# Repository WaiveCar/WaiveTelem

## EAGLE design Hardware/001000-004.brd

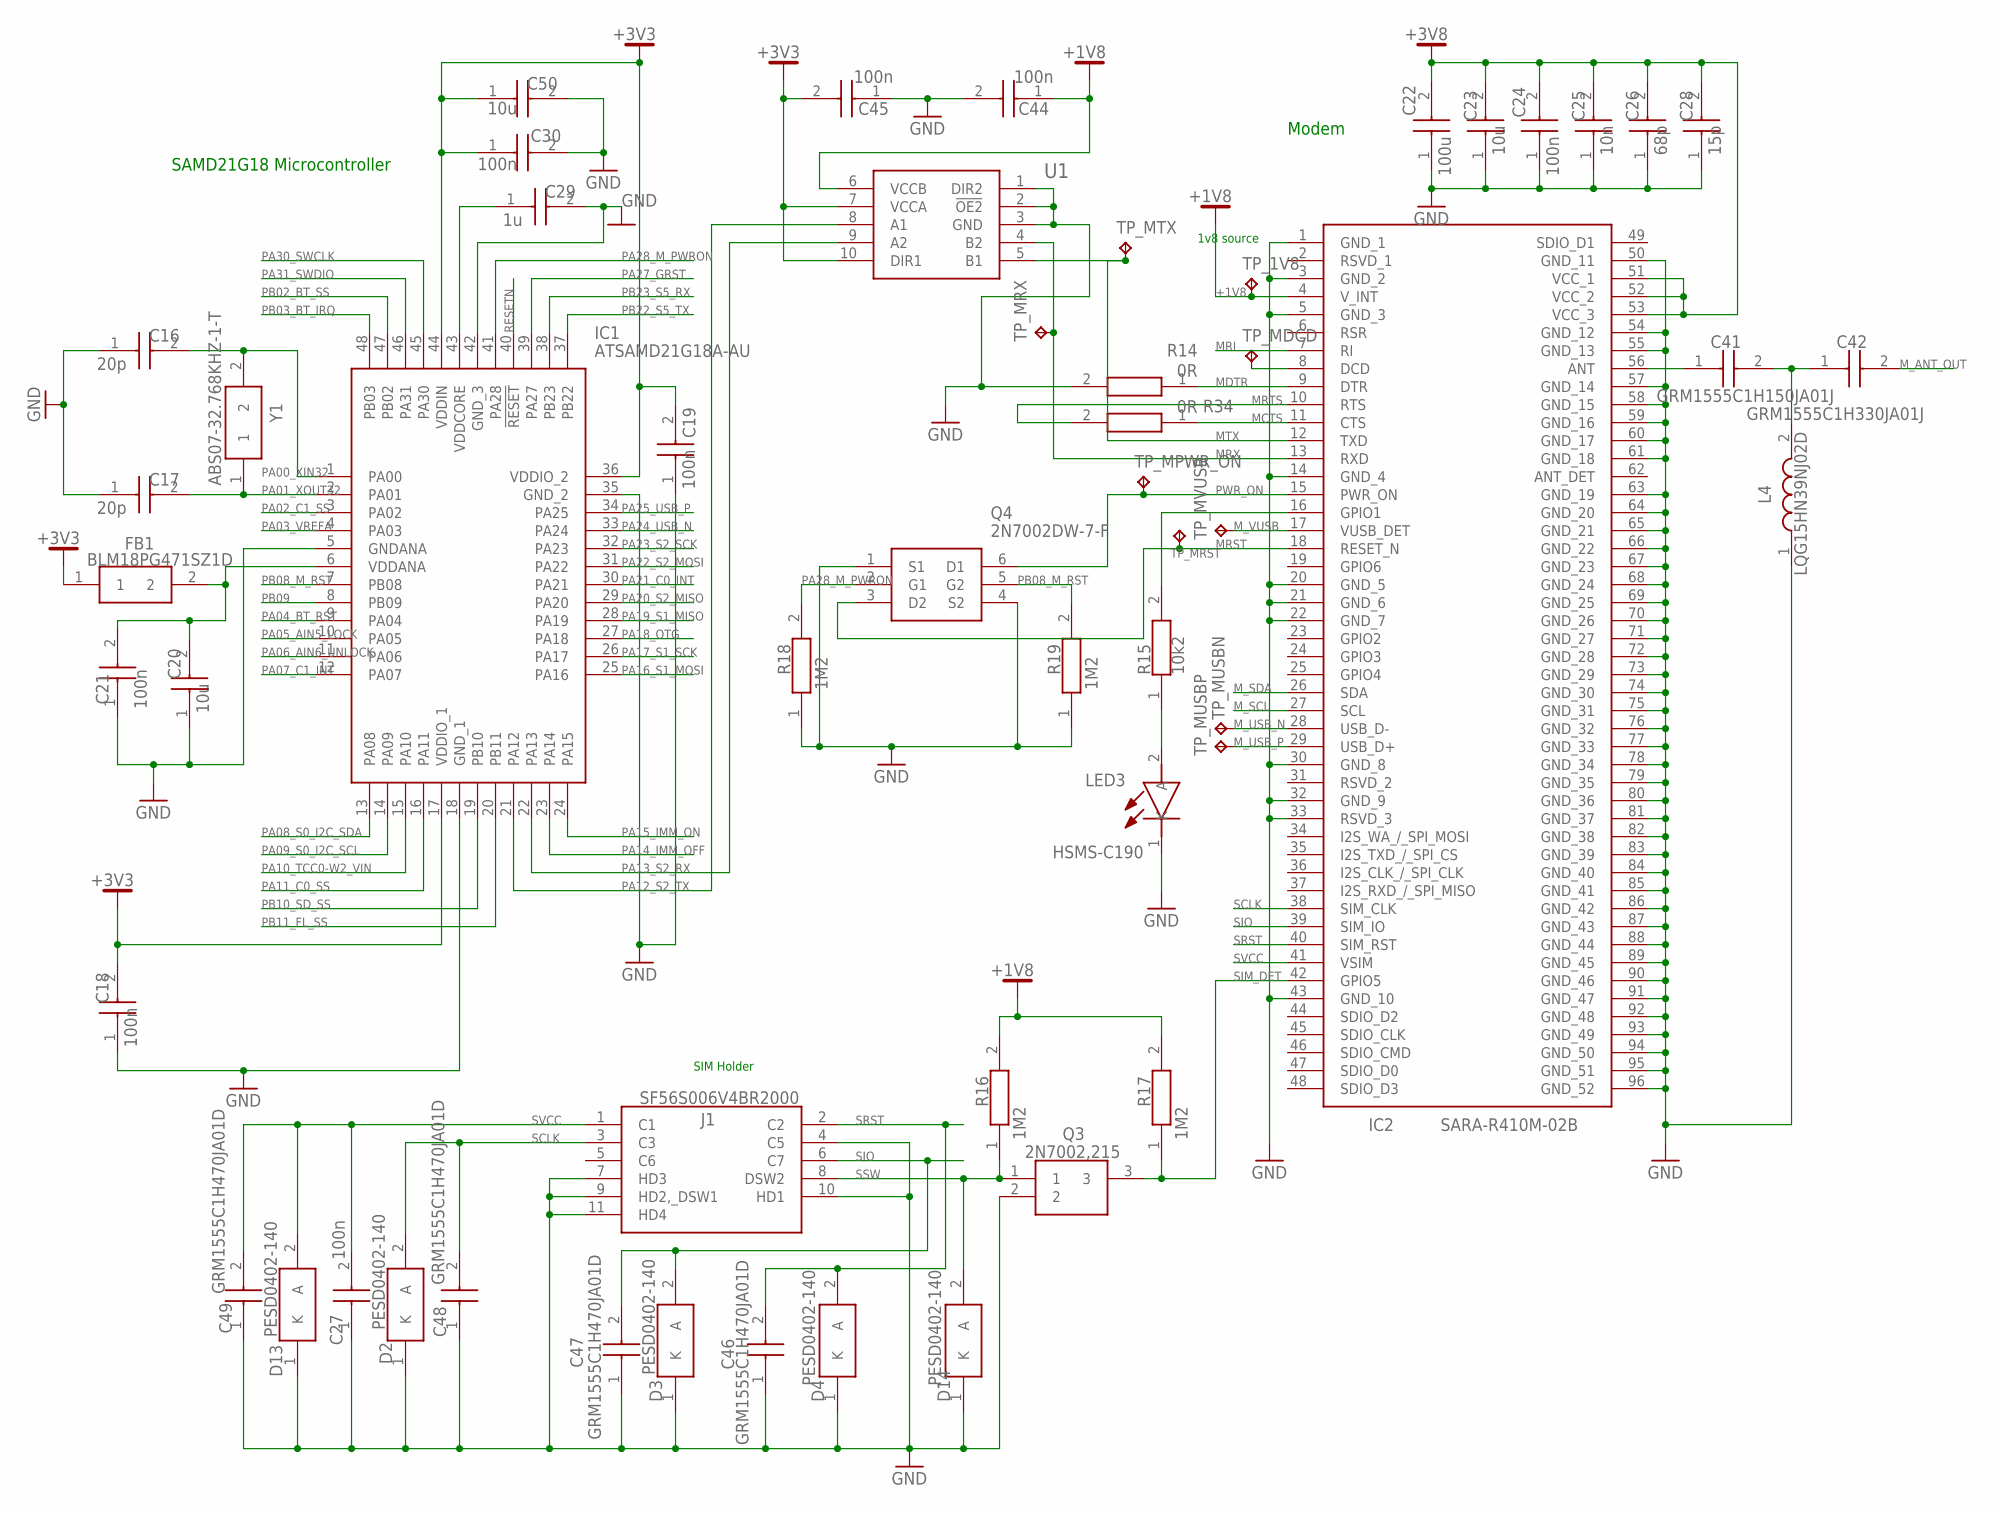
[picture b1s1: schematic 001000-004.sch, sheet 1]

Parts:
C16, C17: 20p; CAPC1005X55N
C18, C19, C21, C24, C27, C30, C44, C45: 100n; CAPC1005X55N
C20, C23, C50: 10u; CAPC1608X90N
C22: 100u; CAPC3216X180N
C25: 10n; CAPC1005X55N
C26: 68p; CAPC1005X55N
C28: 15p; CAPC1005X55N
C29: 1u; CAPC1005X55N
C41: GRM1555C1H150JA01J; CAPC1005X55N
C42: GRM1555C1H330JA01J; CAPC1005X55N
C46, C47, C48, C49: GRM1555C1H470JA01D; CAPC1005X55N
D2, D3, D4, D13, D14: PESD0402-140; DIONC1005X43N
FB1: BLM18PG471SZ1D; BEADC1608X95N
IC1: ATSAMD21G18A-AU; QFP50P900X900X120-48N
IC2: SARA-R410M-02B; SARA-U201-03B
J1: SF56S006V4BR2000
L4: LQG15HN39NJ02D; INDC1005X55N
LED3: HSMS-C190; LEDC1608X90N
Q3: 2N7002,215; SOT95P230X110-3N
Q4: 2N7002DW-7-F; SOT65P210X100-6N
R14, R34: 0R; RESC1005X40N
R15: 10k2; RESC1005X40N
R16, R17, R18, R19: 1M2; RESC1005X40N
TP_1V8: TPB1,27; B1,27
TP_MDCD: TPB1,27; B1,27
TP_MPWR_ON: TPB1,27; B1,27
TP_MRST: TPB1,27; B1,27
TP_MRX: TPB1,27; B1,27
TP_MTX: TPB1,27; B1,27
TP_MUSBN: TPB1,27; B1,27
TP_MUSBP: TPB1,27; B1,27
TP_MVUSB: TPB1,27; B1,27
U1: SN74AVC2T245RSWR; RSW(RPUQFNN10)
Y1: ABS07-32.768KHZ-1-T; ABS0716632768KHZT

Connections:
+1V8: C44.1, IC2.4 (V_INT), R16.2, R17.2, TP_1V8.TP, U1.6 (VCCB)
+3V3: C18.2, C19.2, C30.1, C45.2, C50.1, FB1.1, IC1.17 (VDDIO_1), IC1.36 (VDDIO_2), IC1.44 (VDDIN), U1.7 (VCCA), U1.10 (DIR1); also elsewhere on the board
+3V8: C22.2, C23.2, C24.2, C25.2, C26.2, C28.2, IC2.51 (VCC_1), IC2.52 (VCC_2), IC2.53 (VCC_3); also elsewhere on the board
GND: C16.1, C17.1, C18.1, C19.1, C20.1, C21.1, C22.1, C23.1, C24.1, C25.1, C26.1, C27.1, C28.1, C29.2, C30.2, C44.2, C45.1, C46.1, C47.1, C48.1, C49.1, C50.2, D2.1 (K), D3.1 (K), D4.1 (K), D13.1 (K), D14.1 (K), IC1.5 (GNDANA), IC1.18 (GND_1), IC1.35 (GND_2), IC1.42 (GND_3), IC2.1 (GND_1), IC2.3 (GND_2), IC2.5 (GND_3), IC2.14 (GND_4), IC2.20 (GND_5), IC2.21 (GND_6), IC2.22 (GND_7), IC2.30 (GND_8), IC2.32 (GND_9), IC2.33 (RSVD_3), IC2.43 (GND_10), IC2.50 (GND_11), IC2.54 (GND_12), IC2.55 (GND_13), IC2.57 (GND_14), IC2.58 (GND_15), IC2.59 (GND_16), IC2.60 (GND_17), IC2.61 (GND_18), IC2.63 (GND_19), IC2.64 (GND_20), IC2.65 (GND_21), IC2.66 (GND_22), IC2.67 (GND_23), IC2.68 (GND_24), IC2.69 (GND_25), IC2.70 (GND_26), IC2.71 (GND_27), IC2.72 (GND_28), IC2.73 (GND_29), IC2.74 (GND_30), IC2.75 (GND_31), IC2.76 (GND_32), IC2.77 (GND_33), IC2.78 (GND_34), IC2.79 (GND_35), IC2.80 (GND_36), IC2.81 (GND_37), IC2.82 (GND_38), IC2.83 (GND_39), IC2.84 (GND_40), IC2.85 (GND_41), IC2.86 (GND_42), IC2.87 (GND_43), IC2.88 (GND_44), IC2.89 (GND_45), IC2.90 (GND_46), IC2.91 (GND_47), IC2.92 (GND_48), IC2.93 (GND_49), IC2.94 (GND_50), IC2.95 (GND_51), IC2.96 (GND_52), J1.4 (C5), J1.7 (HD3), J1.9 (HD2,_DSW1), J1.10 (HD1), J1.11 (HD4), L4.1, LED3.1 (K), Q3.2, Q4.1 (S1), Q4.4 (S2), R14.2, R18.1, R19.1, U1.1 (DIR2), U1.2 (!OE2), U1.3 (GND); also elsewhere on the board
MCTS: IC2.11 (CTS), R34.1
MDTR: IC2.9 (DTR), R14.1
MRI: IC2.7 (RI)
MRST: IC2.18 (RESET_N), Q4.3 (D2), TP_MRST.TP
MRTS: IC2.10 (RTS), R34.2
MRX: IC2.13 (RXD), TP_MRX.TP, U1.4 (B2)
MTX: IC2.12 (TXD), TP_MTX.TP, U1.5 (B1)
M_ANT_OUT: C42.2; also elsewhere on the board
M_SCL: IC2.27 (SCL); also elsewhere on the board
M_SDA: IC2.26 (SDA); also elsewhere on the board
M_USB_N: IC2.28 (USB_D-), TP_MUSBN.TP
M_USB_P: IC2.29 (USB_D+), TP_MUSBP.TP
M_VUSB: IC2.17 (VUSB_DET), TP_MVUSB.TP
unnamed: C20.2, C21.2, FB1.2, IC1.6 (VDDANA)
unnamed: C41.1, IC2.56 (ANT)
unnamed: IC2.16 (GPIO1), R15.2
unnamed: LED3.2 (A), R15.1
unnamed: IC2.8 (DCD), TP_MDCD.TP
unnamed: C29.1, IC1.43 (VDDCORE)
unnamed: C41.2, C42.1, L4.2
PA00_XIN32: C16.2, IC1.1 (PA00), Y1.2
PA01_XOUT32: C17.2, IC1.2 (PA01), Y1.1
PA02_C1_SS: IC1.3 (PA02); also elsewhere on the board
PA03_VREFA: IC1.4 (PA03)
PA04_BT_RST: IC1.9 (PA04); also elsewhere on the board
PA05_AIN5_LOCK: IC1.10 (PA05); also elsewhere on the board
PA06_AIN6_UNLOCK: IC1.11 (PA06); also elsewhere on the board
PA07_C1_INT: IC1.12 (PA07); also elsewhere on the board
PA08_S0_I2C_SDA: IC1.13 (PA08); also elsewhere on the board
PA09_S0_I2C_SCL: IC1.14 (PA09); also elsewhere on the board
PA10_TCC0-W2_VIN: IC1.15 (PA10); also elsewhere on the board
PA11_C0_SS: IC1.16 (PA11); also elsewhere on the board
PA12_S2_TX: IC1.21 (PA12), U1.8 (A1)
PA13_S2_RX: IC1.22 (PA13), U1.9 (A2)
PA14_IMM_OFF: IC1.23 (PA14); also elsewhere on the board
PA15_IMM_ON: IC1.24 (PA15); also elsewhere on the board
PA16_S1_MOSI: IC1.25 (PA16); also elsewhere on the board
PA17_S1_SCK: IC1.26 (PA17); also elsewhere on the board
PA18_OTG: IC1.27 (PA18); also elsewhere on the board
PA19_S1_MISO: IC1.28 (PA19); also elsewhere on the board
PA20_S2_MISO: IC1.29 (PA20); also elsewhere on the board
PA21_C0_INT: IC1.30 (PA21); also elsewhere on the board
PA22_S2_MOSI: IC1.31 (PA22); also elsewhere on the board
PA23_S2_SCK: IC1.32 (PA23); also elsewhere on the board
PA24_USB_N: IC1.33 (PA24); also elsewhere on the board
PA25_USB_P: IC1.34 (PA25); also elsewhere on the board
PA27_GRST: IC1.39 (PA27); also elsewhere on the board
PA28_M_PWRON: IC1.41 (PA28), Q4.2 (G1), R18.2
PA30_SWCLK: IC1.45 (PA30); also elsewhere on the board
PA31_SWDIO: IC1.46 (PA31); also elsewhere on the board
PB02_BT_SS: IC1.47 (PB02); also elsewhere on the board
PB03_BT_IRQ: IC1.48 (PB03); also elsewhere on the board
PB08_M_RST: IC1.7 (PB08), Q4.5 (G2), R19.2
PB09: IC1.8 (PB09); also elsewhere on the board
PB10_SD_SS: IC1.19 (PB10); also elsewhere on the board
PB11_FL_SS: IC1.20 (PB11); also elsewhere on the board
PB22_S5_TX: IC1.37 (PB22); also elsewhere on the board
PB23_S5_RX: IC1.38 (PB23); also elsewhere on the board
PWR_ON: IC2.15 (PWR_ON), Q4.6 (D1), TP_MPWR_ON.TP
RESETN: IC1.40 (!RESET); also elsewhere on the board
SCLK: C48.2, D2.2 (A), IC2.38 (SIM_CLK), J1.3 (C3)
SIM_DET: IC2.42 (GPIO5), Q3.3, R17.1
SIO: C47.2, D3.2 (A), IC2.39 (SIM_IO), J1.6 (C7)
SRST: C46.2, D4.2 (A), IC2.40 (SIM_RST), J1.2 (C2)
SSW: D14.2 (A), J1.8 (DSW2), Q3.1, R16.1
SVCC: C27.2, C49.2, D13.2 (A), IC2.41 (VSIM), J1.1 (C1)

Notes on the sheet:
SAMD21G18 Microcontroller
Modem
1v8 source
SIM Holder

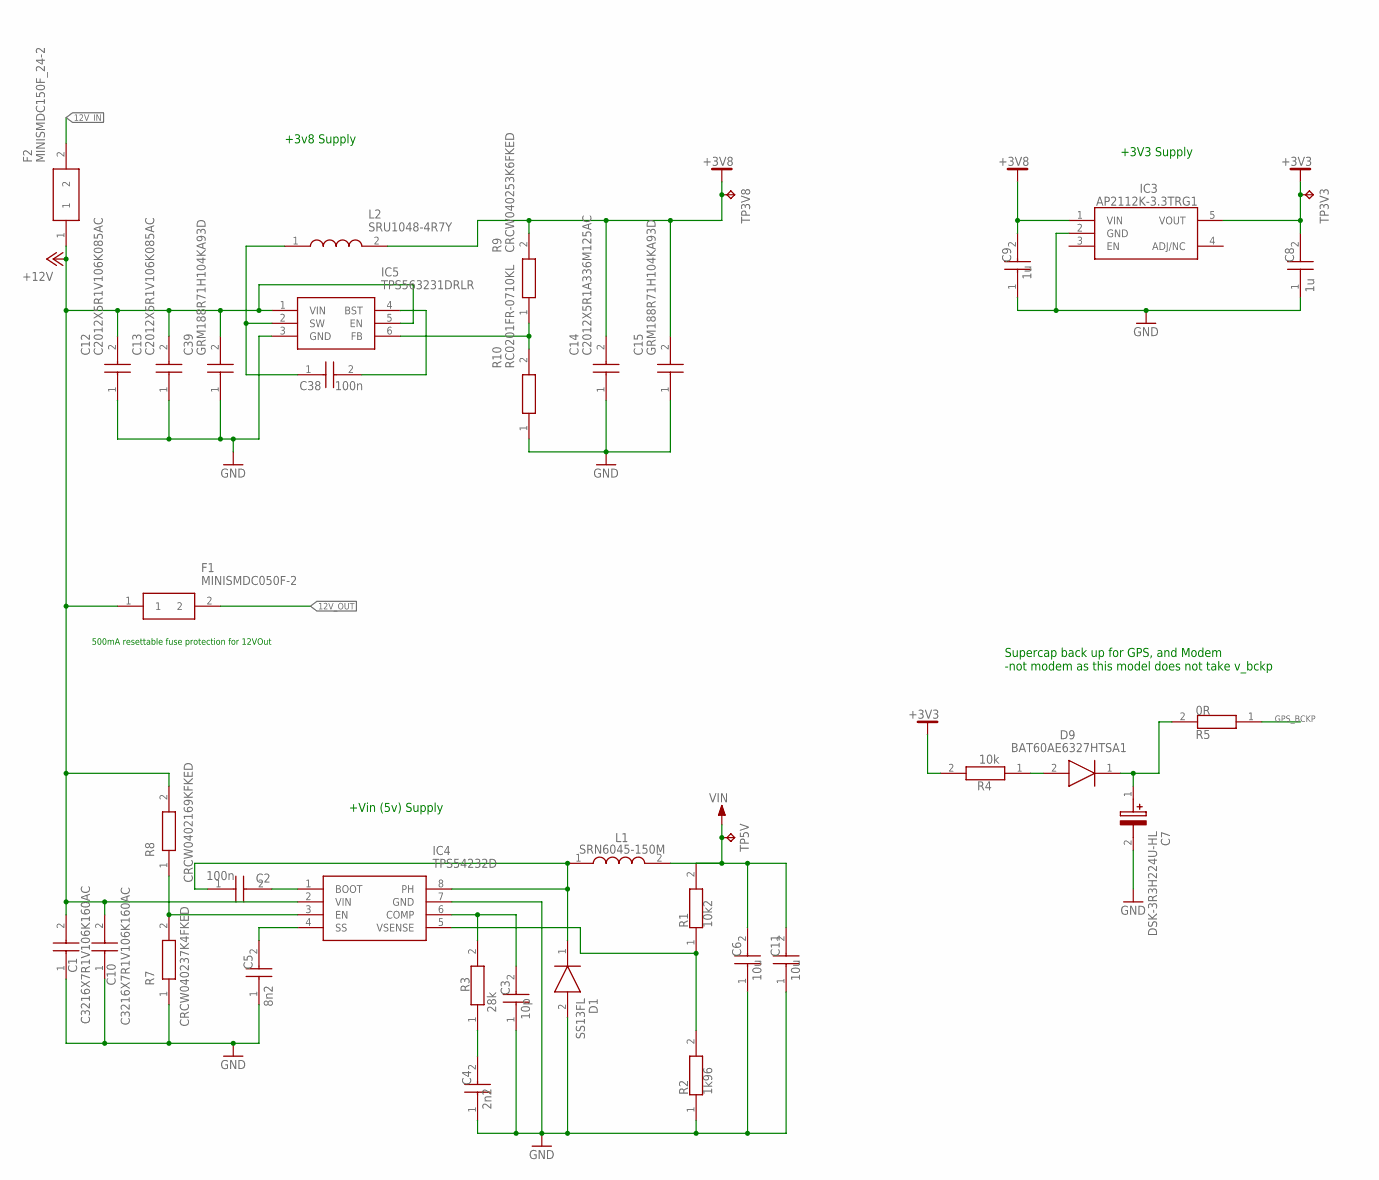
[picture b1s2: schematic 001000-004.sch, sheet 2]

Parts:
C1, C10: C3216X7R1V106K160AC; CAPC3216X180N
C2, C38: 100n; CAPC1005X55N
C3: 10p; CAPC1005X55N
C4: 2n2; CAPC1005X55N
C5: 8n2; CAPC1005X55N
C6, C11: 10u; CAPC2012X145N
C7: DSK-3R3H224U-HL; DSK-414_HL
C8, C9: 1u; CAPC1005X55N
C12, C13: C2012X5R1V106K085AC; CAPC2012X100N
C14: C2012X5R1A336M125AC; CAPC2012X145N
C15, C39: GRM188R71H104KA93D; CAPC1608X90N
D1: SS13FL; SODFL3617X108N
D9: BAT60AE6327HTSA1; SOD2513X110N
F1: MINISMDC050F-2; FUSC4632X62N
F2: MINISMDC150F_24-2; FUSC4632X194N
IC3: AP2112K-3.3TRG1; SOT95P282X130-5N
IC4: TPS54232D; SOIC127P600X175-8N
IC5: TPS563231DRLR; SOTFL50P160X60-6N
L1: SRN6045-150M; SRN6045_1
L2: SRU1048-4R7Y; SRU10484R7Y
R1: 10k2; RESC1005X40N
R2: 1k96; RESC1005X40N
R3: 28k; RESC1005X40N
R4: 10k; RESC1508X50N
R5: 0R; RESC1005X40N
R7: CRCW040237K4FKED; RESC1005X40N
R8: CRCW0402169KFKED; RESC1005X40N
R9: CRCW040253K6FKED; RESC1005X40N
R10: RC0201FR-0710KL; RESC0603X26N
TP3V3, TP3V8, TP5V: TPB1,27; B1,27

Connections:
12V_IN: F2.2; also elsewhere on the board
12V_OUT: F1.2; also elsewhere on the board
+3V3: C8.2, IC3.5 (VOUT), R4.2, TP3V3.TP; also elsewhere on the board
+3V8: C9.2, C14.2, C15.2, IC3.1 (VIN), L2.2, R9.2, TP3V8.TP; also elsewhere on the board
+12V: C1.2, C10.2, C12.2, C13.2, C39.2, F1.1, F2.1, IC4.2 (VIN), IC5.1 (VIN), IC5.5 (EN), R8.2; also elsewhere on the board
GND: C1.1, C3.1, C4.1, C5.1, C6.1, C7.2 (+), C8.1, C9.1, C10.1, C11.1, C12.1, C13.1, C14.1, C15.1, C39.1, D1.2 (A), IC3.2 (GND), IC4.7 (GND), IC5.3 (GND), R2.1, R7.1, R10.1; also elsewhere on the board
GPS_BCKP: R5.1; also elsewhere on the board
unnamed: C2.2, IC4.1 (BOOT)
unnamed: C2.1, D1.1 (K), IC4.8 (PH), L1.1
unnamed: C3.2, IC4.6 (COMP), R3.2
unnamed: C4.2, R3.1
unnamed: IC4.5 (VSENSE), R1.1, R2.2
unnamed: D9.2 (A), R4.1
unnamed: C5.2, IC4.4 (SS)
unnamed: C7.1 (-), D9.1 (K), R5.2
unnamed: IC4.3 (EN), R7.2, R8.1
unnamed: C38.1, IC5.2 (SW), L2.1
unnamed: IC5.6 (FB), R9.1, R10.2
unnamed: C38.2, IC5.4 (BST)
VIN: C6.2, C11.2, L1.2, R1.2, TP5V.TP; also elsewhere on the board

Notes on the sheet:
Supercap back up for GPS, and Modem -not modem as this model does not take v_bckp
+3V3 Supply
+Vin (5v) Supply
+3v8 Supply
500mA resettable fuse protection for 12VOut

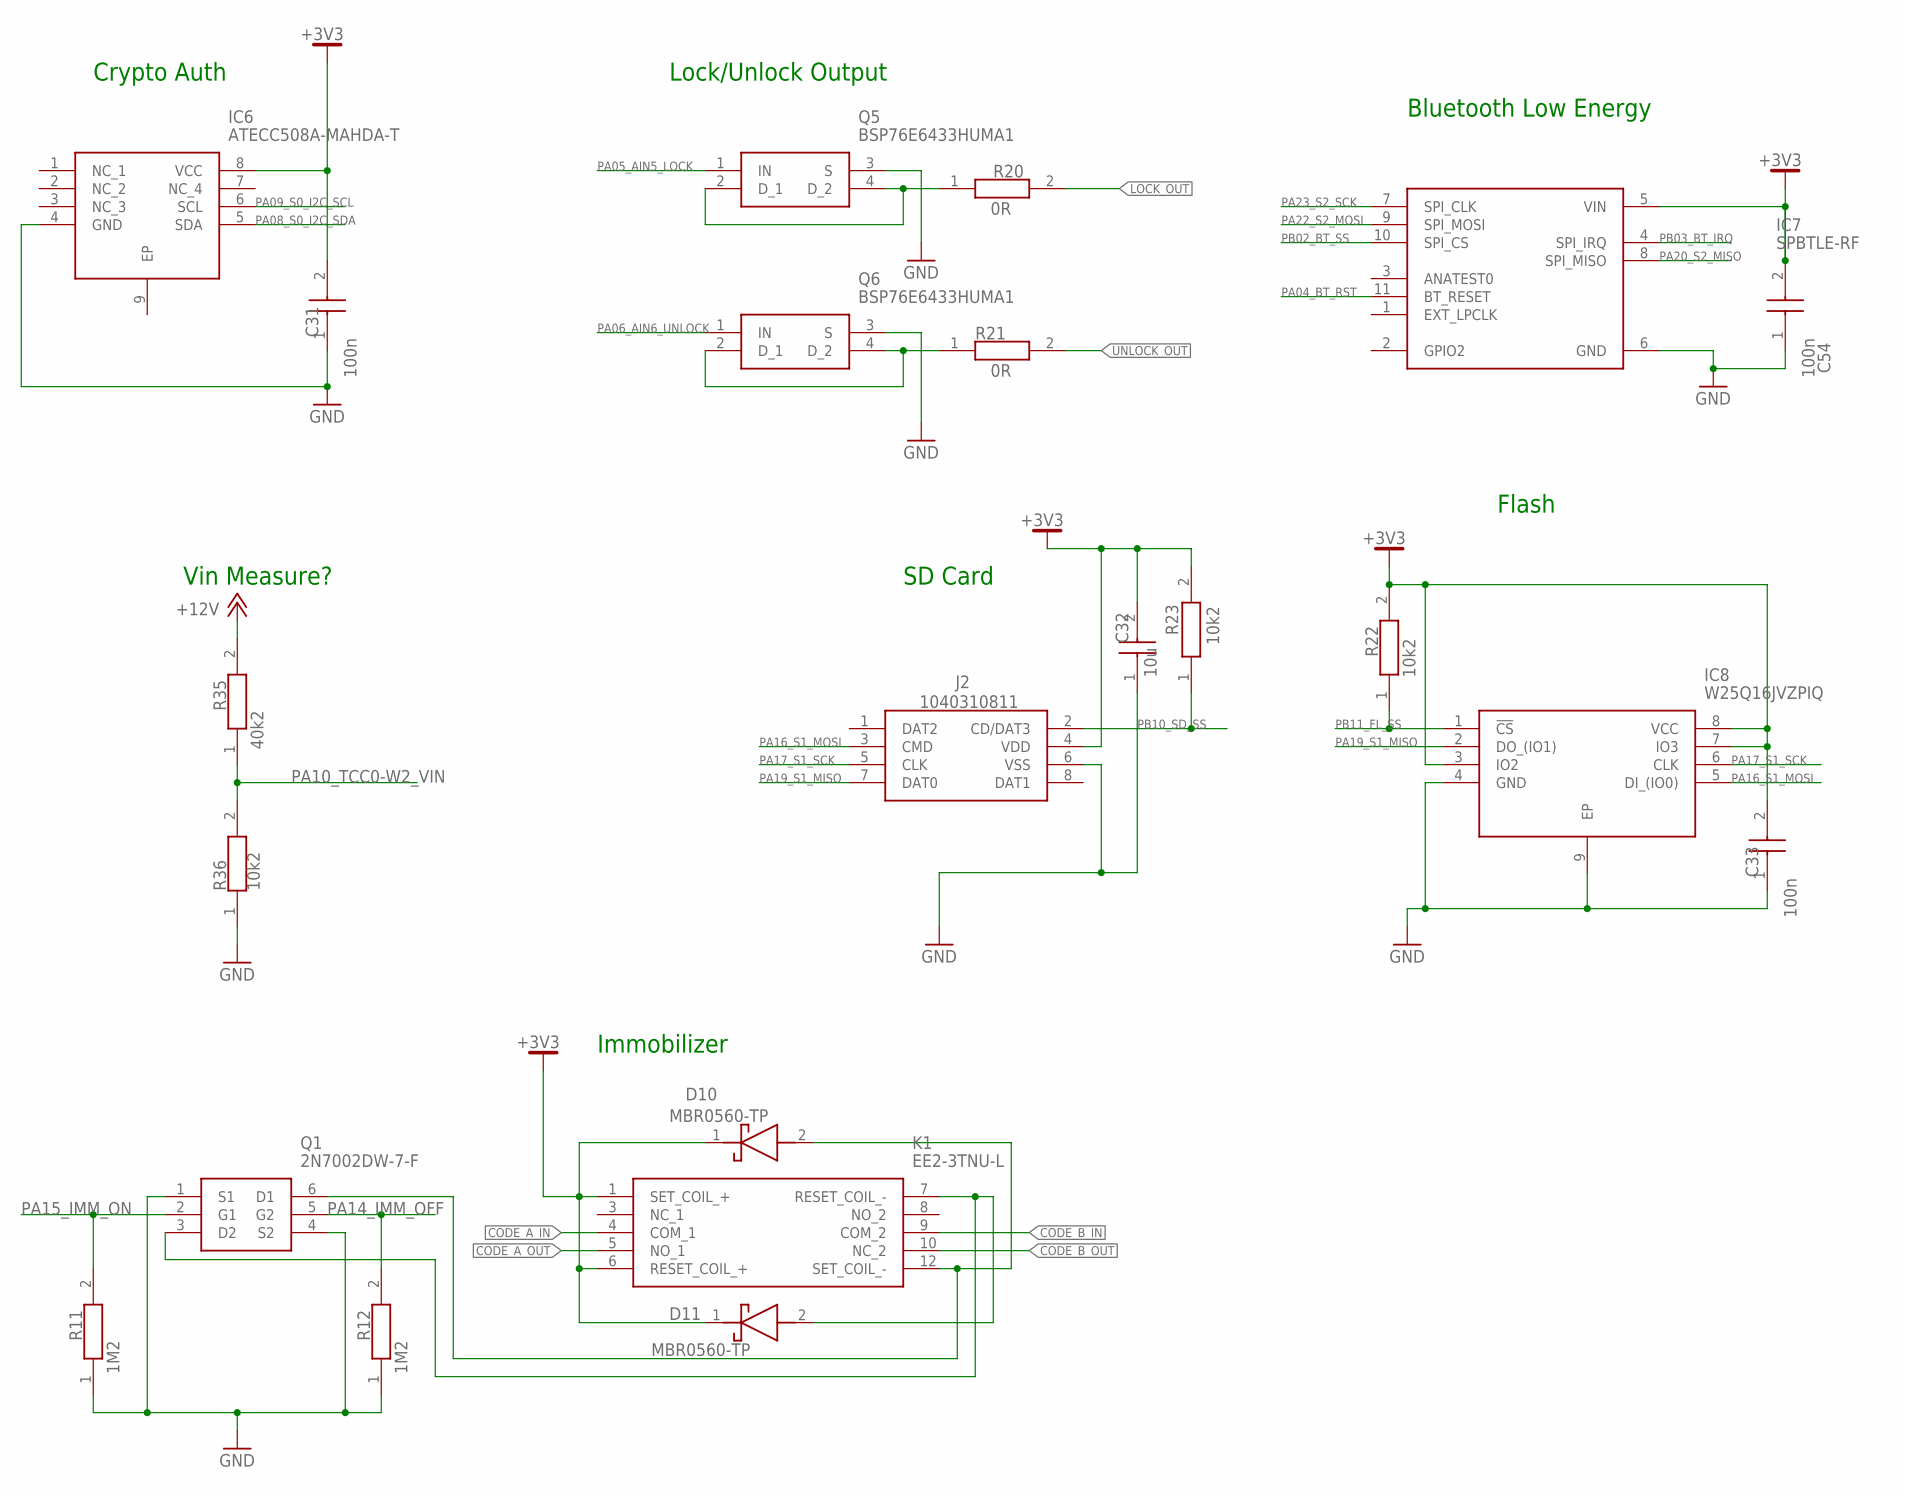
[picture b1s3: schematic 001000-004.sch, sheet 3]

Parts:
C31, C33, C54: 100n; CAPC1005X55N
C32: 10u; CAPC1005X55N
D10, D11: MBR0560-TP; SOD3716X135N
IC6: ATECC508A-MAHDA-T; SON50P300X200X60-9N
IC7: SPBTLE-RF; XCVR_SPBTLE-RF
IC8: W25Q16JVZPIQ; SON127P600X500X80-9N
J2: 1040310811
K1: EE2-3TNU-L; EE25TNU
Q1: 2N7002DW-7-F; SOT65P210X100-6N
Q5, Q6: BSP76E6433HUMA1; SOT230P700X170-4N
R11, R12: 1M2; RESC1005X40N
R20, R21: 0R; RESC3116X65N
R22, R23, R36: 10k2; RESC1005X40N
R35: 40k2; RESC1005X40N

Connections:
+3V3: C31.2, C32.2, C33.2, C54.2, D10.1 (K), D11.1 (K), IC6.8 (VCC), IC7.5 (VIN), IC8.3 (IO2), IC8.7 (IO3), IC8.8 (VCC), J2.4 (VDD), K1.1 (SET_COIL_+), K1.6 (RESET_COIL_+), R22.2, R23.2; also elsewhere on the board
+12V: R35.2; also elsewhere on the board
CODE_A_IN: K1.4 (COM_1); also elsewhere on the board
CODE_A_OUT: K1.5 (NO_1); also elsewhere on the board
CODE_B_IN: K1.9 (COM_2); also elsewhere on the board
CODE_B_OUT: K1.10 (NC_2); also elsewhere on the board
GND: C31.1, C32.1, C33.1, C54.1, IC6.4 (GND), IC7.6 (GND), IC8.4 (GND), IC8.9 (EP), J2.6 (VSS), Q1.1 (S1), Q1.4 (S2), Q5.3 (S), Q6.3 (S), R11.1, R12.1, R36.1; also elsewhere on the board
LOCK_OUT: R20.2; also elsewhere on the board
unnamed: D11.2 (A), K1.7 (RESET_COIL_-), Q1.3 (D2)
unnamed: D10.2 (A), K1.12 (SET_COIL_-), Q1.6 (D1)
unnamed: Q6.2 (D_1), Q6.4 (D_2), R21.1
unnamed: Q5.2 (D_1), Q5.4 (D_2), R20.1
PA04_BT_RST: IC7.11 (BT_RESET); also elsewhere on the board
PA05_AIN5_LOCK: Q5.1 (IN); also elsewhere on the board
PA06_AIN6_UNLOCK: Q6.1 (IN); also elsewhere on the board
PA08_S0_I2C_SDA: IC6.5 (SDA); also elsewhere on the board
PA09_S0_I2C_SCL: IC6.6 (SCL); also elsewhere on the board
PA10_TCC0-W2_VIN: R35.1, R36.2; also elsewhere on the board
PA14_IMM_OFF: Q1.5 (G2), R12.2; also elsewhere on the board
PA15_IMM_ON: Q1.2 (G1), R11.2; also elsewhere on the board
PA16_S1_MOSI: IC8.5 (DI_(IO0)), J2.3 (CMD); also elsewhere on the board
PA17_S1_SCK: IC8.6 (CLK), J2.5 (CLK); also elsewhere on the board
PA19_S1_MISO: IC8.2 (DO_(IO1)), J2.7 (DAT0); also elsewhere on the board
PA20_S2_MISO: IC7.8 (SPI_MISO); also elsewhere on the board
PA22_S2_MOSI: IC7.9 (SPI_MOSI); also elsewhere on the board
PA23_S2_SCK: IC7.7 (SPI_CLK); also elsewhere on the board
PB02_BT_SS: IC7.10 (SPI_CS); also elsewhere on the board
PB03_BT_IRQ: IC7.4 (SPI_IRQ); also elsewhere on the board
PB10_SD_SS: J2.2 (CD/DAT3), R23.1; also elsewhere on the board
PB11_FL_SS: IC8.1 (!CS), R22.1; also elsewhere on the board
UNLOCK_OUT: R21.2; also elsewhere on the board

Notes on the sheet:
Crypto Auth
Lock/Unlock Output
Bluetooth Low Energy
SD Card
Immobilizer
Flash
Vin Measure?

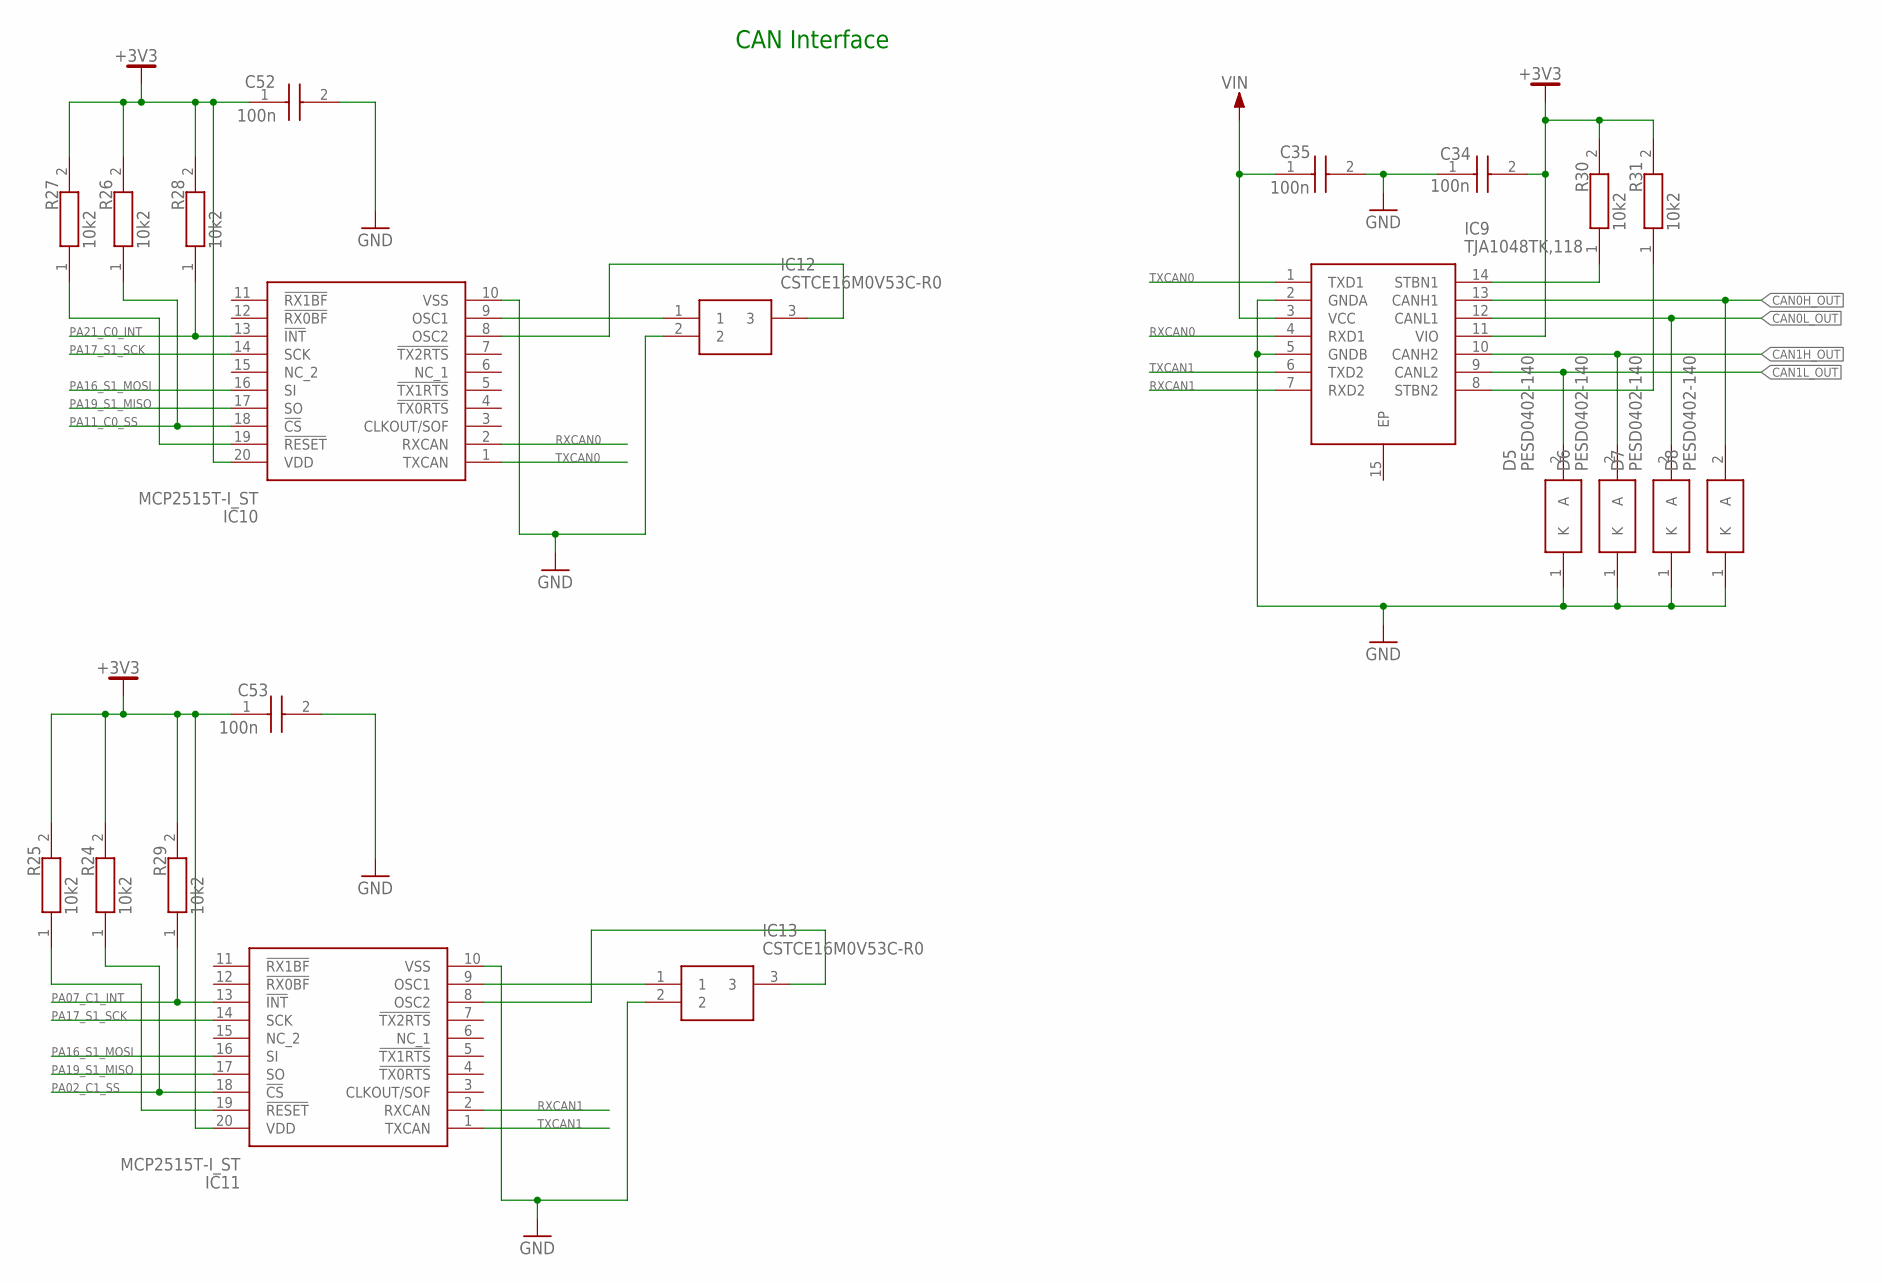
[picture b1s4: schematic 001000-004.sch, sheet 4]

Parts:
C34, C35, C52, C53: 100n; CAPC1005X55N
D5, D6, D7, D8: PESD0402-140; DIONC1005X43N
IC9: TJA1048TK,118; SON65P300X450X100-15N
IC10, IC11: MCP2515T-I_ST; SOP65P640X120-20N
IC12, IC13: CSTCE16M0V53C-R0; CSTCE16M0V53CR0
R24, R25, R26, R27, R28, R29, R30, R31: 10k2; RESC1005X40N

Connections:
+3V3: C34.2, C52.1, C53.1, IC9.11 (VIO), IC10.20 (VDD), IC11.20 (VDD), R24.2, R25.2, R26.2, R27.2, R28.2, R29.2, R30.2, R31.2; also elsewhere on the board
CAN0H_OUT: D8.2 (A), IC9.13 (CANH1); also elsewhere on the board
CAN0L_OUT: D7.2 (A), IC9.12 (CANL1); also elsewhere on the board
CAN1H_OUT: D6.2 (A), IC9.10 (CANH2); also elsewhere on the board
CAN1L_OUT: D5.2 (A), IC9.9 (CANL2); also elsewhere on the board
GND: C34.1, C35.2, C52.2, C53.2, D5.1 (K), D6.1 (K), D7.1 (K), D8.1 (K), IC9.2 (GNDA), IC9.5 (GNDB), IC10.10 (VSS), IC11.10 (VSS), IC12.2, IC13.2; also elsewhere on the board
unnamed: IC10.9 (OSC1), IC12.1
unnamed: IC10.8 (OSC2), IC12.3
unnamed: IC9.14 (STBN1), R30.1
unnamed: IC11.9 (OSC1), IC13.1
unnamed: IC11.8 (OSC2), IC13.3
unnamed: IC9.8 (STBN2), R31.1
unnamed: IC11.19 (!RESET), R25.1
unnamed: IC10.19 (!RESET), R27.1
PA02_C1_SS: IC11.18 (!CS), R24.1; also elsewhere on the board
PA07_C1_INT: IC11.13 (!INT), R29.1; also elsewhere on the board
PA11_C0_SS: IC10.18 (!CS), R26.1; also elsewhere on the board
PA16_S1_MOSI: IC10.16 (SI), IC11.16 (SI); also elsewhere on the board
PA17_S1_SCK: IC10.14 (SCK), IC11.14 (SCK); also elsewhere on the board
PA19_S1_MISO: IC10.17 (SO), IC11.17 (SO); also elsewhere on the board
PA21_C0_INT: IC10.13 (!INT), R28.1; also elsewhere on the board
RXCAN0: IC9.4 (RXD1), IC10.2 (RXCAN)
RXCAN1: IC9.7 (RXD2), IC11.2 (RXCAN)
TXCAN0: IC9.1 (TXD1), IC10.1 (TXCAN)
TXCAN1: IC9.6 (TXD2), IC11.1 (TXCAN)
VIN: C35.1, IC9.3 (VCC); also elsewhere on the board

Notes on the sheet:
CAN Interface

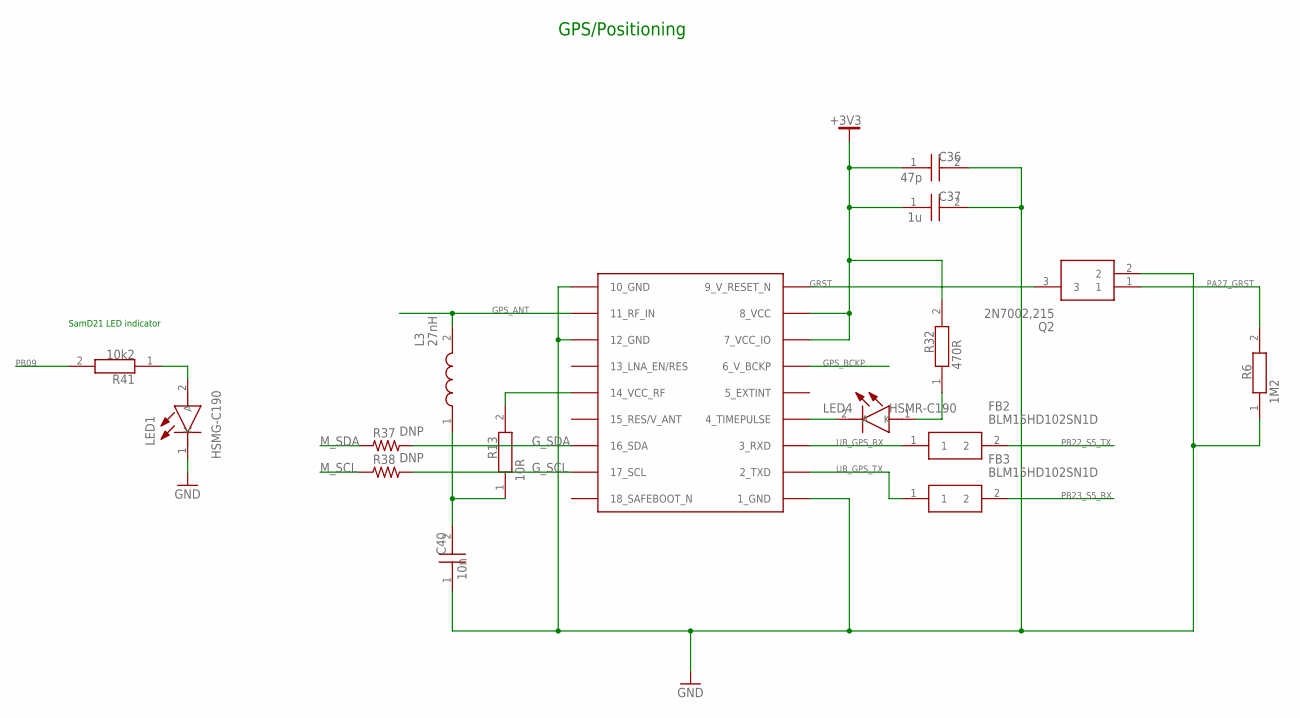
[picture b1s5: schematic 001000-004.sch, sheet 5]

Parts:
C36: 47p; CAPC1005X55N
C37: 1u; CAPC1608X90N
C40: 10n; CAPC1005X55N
FB2, FB3: BLM15HD102SN1D; BEADC1005X55N
L3: 27nH; INDC1608X95N
LED1: HSMG-C190; LEDC1608X90N
LED4: HSMR-C190; LEDC1608X80N
Q2: 2N7002,215; SOT95P230X110-3N
R6: 1M2; RESC1005X40N
R13: 10R; RESC1005X35N
R32: 470R; RESC1005X35N
R37, R38: DNP; R0402
R41: 10k2; RESC1005X40N
U$1: MAX-M8

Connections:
+3V3: C36.1, C37.1, R32.2, U$1.7_VCC_IO, U$1.8_VCC; also elsewhere on the board
GND: C36.2, C37.2, C40.1, LED1.1 (K), Q2.2, R6.1, U$1.1_GND, U$1.10_GND, U$1.12_GND; also elsewhere on the board
GPS_ANT: L3.2, U$1.11_RF_IN; also elsewhere on the board
GPS_BCKP: U$1.6_V_BCKP; also elsewhere on the board
GRST: Q2.3, U$1.9_RESET_N (9_V_RESET_N)
G_SCL: R38.2, U$1.17_SCL
G_SDA: R37.2, U$1.16_SDA
M_SCL: R38.1; also elsewhere on the board
M_SDA: R37.1; also elsewhere on the board
unnamed: LED1.2 (A), R41.1
unnamed: LED4.2 (A), U$1.4_TIMEPULSE
unnamed: LED4.1 (K), R32.1
unnamed: R13.2, U$1.14_VCC_RF
unnamed: C40.2, L3.1, R13.1
PA27_GRST: Q2.1, R6.2; also elsewhere on the board
PB09: R41.2; also elsewhere on the board
PB22_S5_TX: FB2.2; also elsewhere on the board
PB23_S5_RX: FB3.2; also elsewhere on the board
UB_GPS_RX: FB2.1, U$1.3_RXD
UB_GPS_TX: FB3.1, U$1.2_TXD

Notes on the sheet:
GPS/Positioning
SamD21 LED indicator

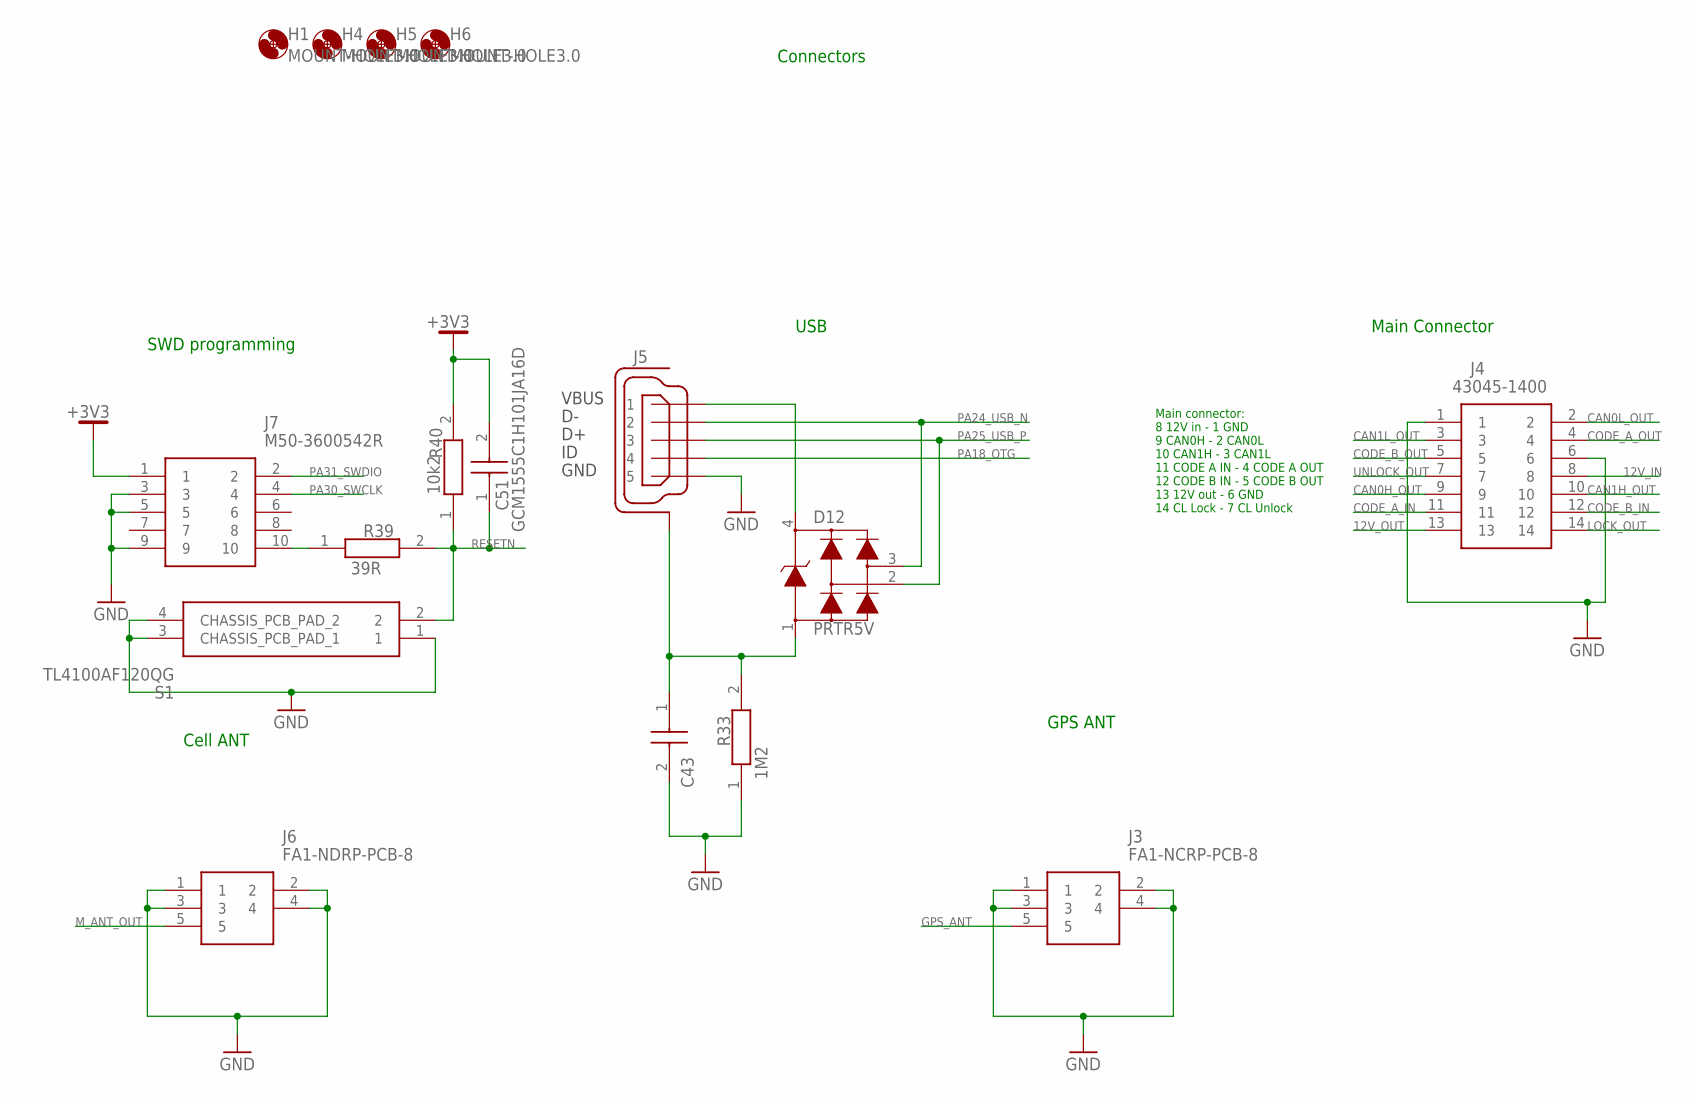
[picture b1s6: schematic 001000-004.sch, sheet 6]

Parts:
C43: 4n7; CAPC1005X55N
C51: GCM1555C1H101JA16D; CAPC1005X55N
D12: PRTR5V; SOT190P230X110-4N
H1, H4, H5, H6: MOUNT-HOLE3.0; 3,0
J3: FA1-NCRP-PCB-8; FA1NCRPPCB8
J4: 43045-1400
J5: -; ZX62-AB-5PA
J6: FA1-NDRP-PCB-8; FA1NDRPPCB8
J7: M50-3600542R; M503600542R
R33: 1M2; RESC1005X40N
R39: 39R; RESC1005X40N
R40: 10k2; RESC1005X40N
S1: TL4100AF120QG

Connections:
12V_IN: J4.8; also elsewhere on the board
12V_OUT: J4.13; also elsewhere on the board
+3V3: C51.2, J7.1, R40.2; also elsewhere on the board
CAN0H_OUT: J4.9; also elsewhere on the board
CAN0L_OUT: J4.2; also elsewhere on the board
CAN1H_OUT: J4.10; also elsewhere on the board
CAN1L_OUT: J4.3; also elsewhere on the board
CODE_A_IN: J4.11; also elsewhere on the board
CODE_A_OUT: J4.4; also elsewhere on the board
CODE_B_IN: J4.12; also elsewhere on the board
CODE_B_OUT: J4.5; also elsewhere on the board
GND: C43.2, J3.1, J3.2, J3.3, J3.4, J4.1, J4.6, J5.5, J6.1, J6.2, J6.3, J6.4, J7.3, J7.5, J7.9, R33.1, S1.1, S1.3 (CHASSIS_PCB_PAD_1), S1.4 (CHASSIS_PCB_PAD_2); also elsewhere on the board
GPS_ANT: J3.5; also elsewhere on the board
LOCK_OUT: J4.14; also elsewhere on the board
M_ANT_OUT: J6.5; also elsewhere on the board
unnamed: J7.10, R39.1
unnamed: D12.4, J5.1
unnamed: C43.1, D12.1, J5.6 (SH), J5.7 (SH), J5.8 (SH), J5.9 (SH), J5.10 (SH), J5.11 (SH), R33.2
PA18_OTG: J5.4; also elsewhere on the board
PA24_USB_N: D12.3, J5.2; also elsewhere on the board
PA25_USB_P: D12.2, J5.3; also elsewhere on the board
PA30_SWCLK: J7.4; also elsewhere on the board
PA31_SWDIO: J7.2; also elsewhere on the board
RESETN: C51.1, R39.2, R40.1, S1.2; also elsewhere on the board
UNLOCK_OUT: J4.7; also elsewhere on the board

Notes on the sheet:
Connectors
SWD programming
USB
Main Connector
Cell ANT
GPS ANT
Main connector: 8 12V in - 1 GND 9 CAN0H - 2 CAN0L 10 CAN1H - 3 CAN1L 11 CODE A IN - 4 CODE A OUT 12 CODE B IN - 5 CODE B OUT 13 12V out - 6 GND 14 CL Lock - 7 CL Unlock

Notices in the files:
parts and their libraries:
rc-master: Copyright (C) 2007, Bob Starr
